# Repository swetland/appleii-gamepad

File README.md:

# Apple II Gamepad

This project contains the PCB design and CAD design for an Apple II Gamepad more in the general style of an SNES controller.

[KiCAD](pcb/) and [FreeCAD](enclosure/) design files are available, as well as [exported](export/) gerbers and STL files suitable for PCB manufacturing and 3D printing.

The electrical design is based largely on information collected and presented in this very helpful [Blondihacks Blog Post](https://blondihacks.com/apple-ii-gamepad-prototype/).

I've manufactured the enclosure with a Prusa MK4 3d Printer (in PLA) as well as via JLCPCB's 3d printing service (in nylon using an SLS process).

### Photos of a fully assembled gamepad

### PCB Components

1x [Two Axis Thumbstuck, Sparkfun](https://www.digikey.com/en/products/detail/sparkfun-electronics/COM-09032/6823623)

2x [Tactile Switch, CUI Devices, TS13-1212-73-BK-160-D](https://www.digikey.com/en/products/detail/cui-devices/TS13-1212-73-BK-160-D/16562837)

2x [Trimmer, 5K, Bournes 3306W-1-502](https://www.digikey.com/en/products/detail/bourns-inc/3306W-1-502/84764)

2x Resistor, 0603, 470 ohm

6x Capacitor, 0603, 100nF (may need adjusting)

2x Header, 0.1", 3 pin

2x Jumper, 0.1"

1x Cable, 6 conductor, ~1 meter

1x DB9 M connector and enclosure

6x Brass heat-set M3 inserts

6x M3 screws

### Limitations

The unit I fully assmbled and tested with an Apple IIe (enhanced), reads 149/135 with the thumbstick in the center position.
The trimmers can increase but not decrease this value.
Adjusting the capacitance should allow more control, but that has to be done by adding/remove capacitors.
As-is, it works great with Lode Runner, and has not been tested extensively otherwise.

### Todo List for Future Revisions

1. A switch to swap buttons

2. A switch or jumper to enable thumbstick button

3. Adjustable Capacitors of some?

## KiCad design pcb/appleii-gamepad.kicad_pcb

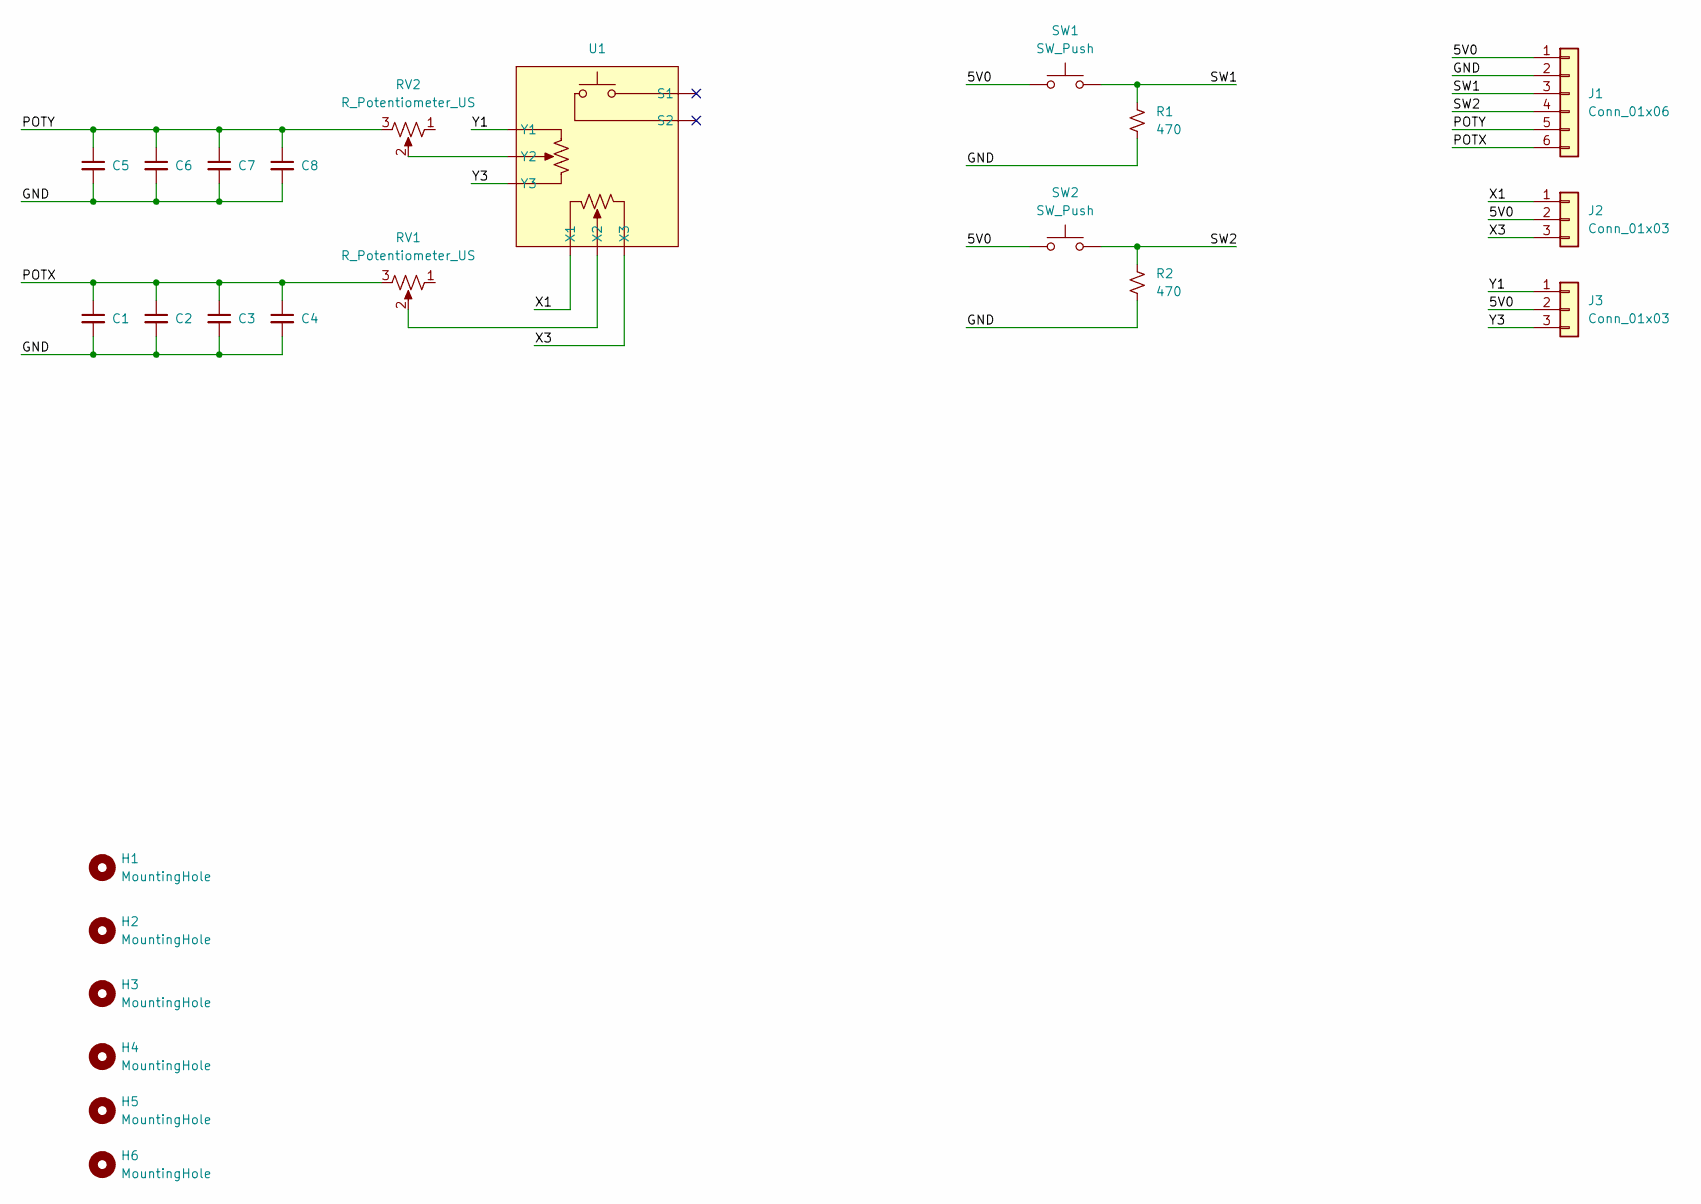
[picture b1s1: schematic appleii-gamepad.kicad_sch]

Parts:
C1, C2, C3, C4, C5, C6, C7, C8: C_Small; C_0603_1608Metric_Pad1.08x0.95mm_HandSolder
H1, H2, H3, H4, H5, H6: MountingHole; MountingHole_3.2mm_M3
J1: Conn_01x06; PinHeader_1x06_P2.54mm_Vertical
J2, J3: Conn_01x03; PinHeader_1x03_P2.54mm_Vertical
R1, R2: 470; R_0603_1608Metric_Pad0.98x0.95mm_HandSolder
RV1, RV2: R_Potentiometer_US; Trim_Pot_Bourns_3306W
SW1, SW2: SW_Push; Tact_Switch_CUI_TS13
U1: Thumbstick

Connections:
/5V0: J1.1, J2.2, J3.2, SW1.1, SW2.1
/GND: C1.2, C2.2, C3.2, C4.2, C5.2, C6.2, C7.2, C8.2, J1.2, R1.2, R2.1
/POTX: C1.1, C2.1, C3.1, C4.1, J1.6, RV1.3
/POTY: C5.1, C6.1, C7.1, C8.1, J1.5, RV2.3
/SW1: J1.3, R1.1, SW1.2
/SW2: J1.4, R2.2, SW2.2
/X1: J2.1, U1.X1
/X3: J2.3, U1.X3
/Y1: J3.1, U1.Y1
/Y3: J3.3, U1.Y3
unnamed: RV1.2, U1.X2
unnamed: RV2.2, U1.Y2

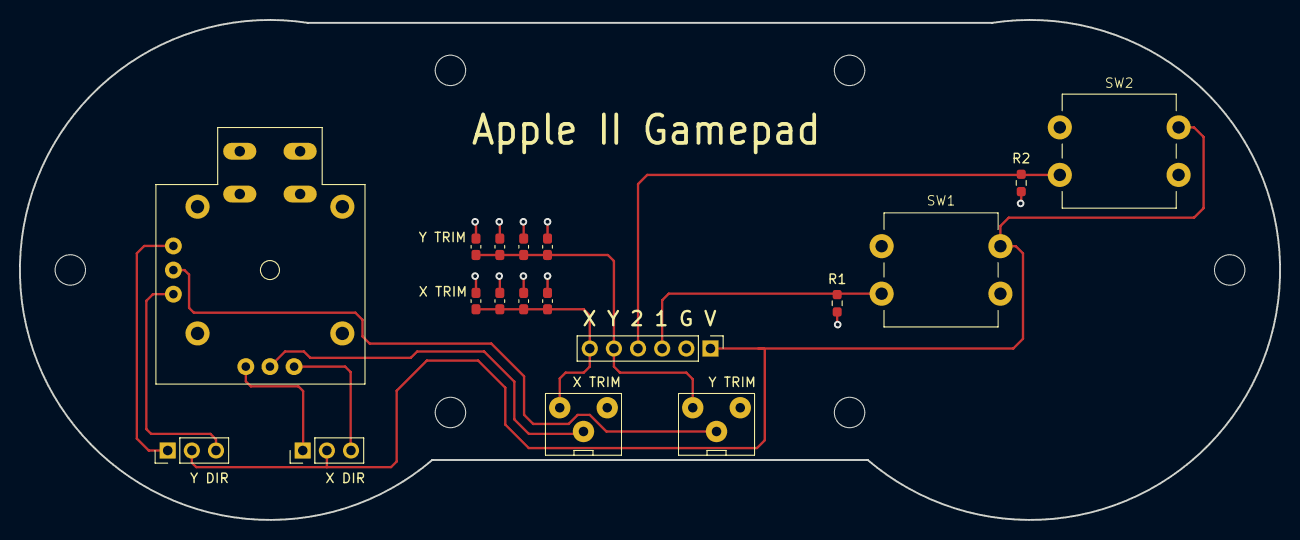
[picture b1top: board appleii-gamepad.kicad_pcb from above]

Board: 2 copper layers, 132.6 x 52.6 mm, 24 parts (0 on the bottom side), 12 nets.

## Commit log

2023-08-01 initial checkin - v1 pcb
2023-08-01 initial checkin - v1 and v1.1 enclosures
    - v1.1 modifies the button to be more FDM-friendly
2023-08-01 gerbers for v1 pcb
2023-08-01 stl files for v1 enclosure
2023-08-01 notes on gamepad connector pinout
2023-08-01 add gitignore and LICENSE files
2023-08-01 add readme and some photos
2023-08-01 add mechanical components to list
